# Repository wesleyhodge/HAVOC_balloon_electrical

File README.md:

# HAVOC\_balloon\_electrical

contains Kicad files for HAVOC

4.0 is the current 4.0 board

V3 is the eclipse model of HAVOC

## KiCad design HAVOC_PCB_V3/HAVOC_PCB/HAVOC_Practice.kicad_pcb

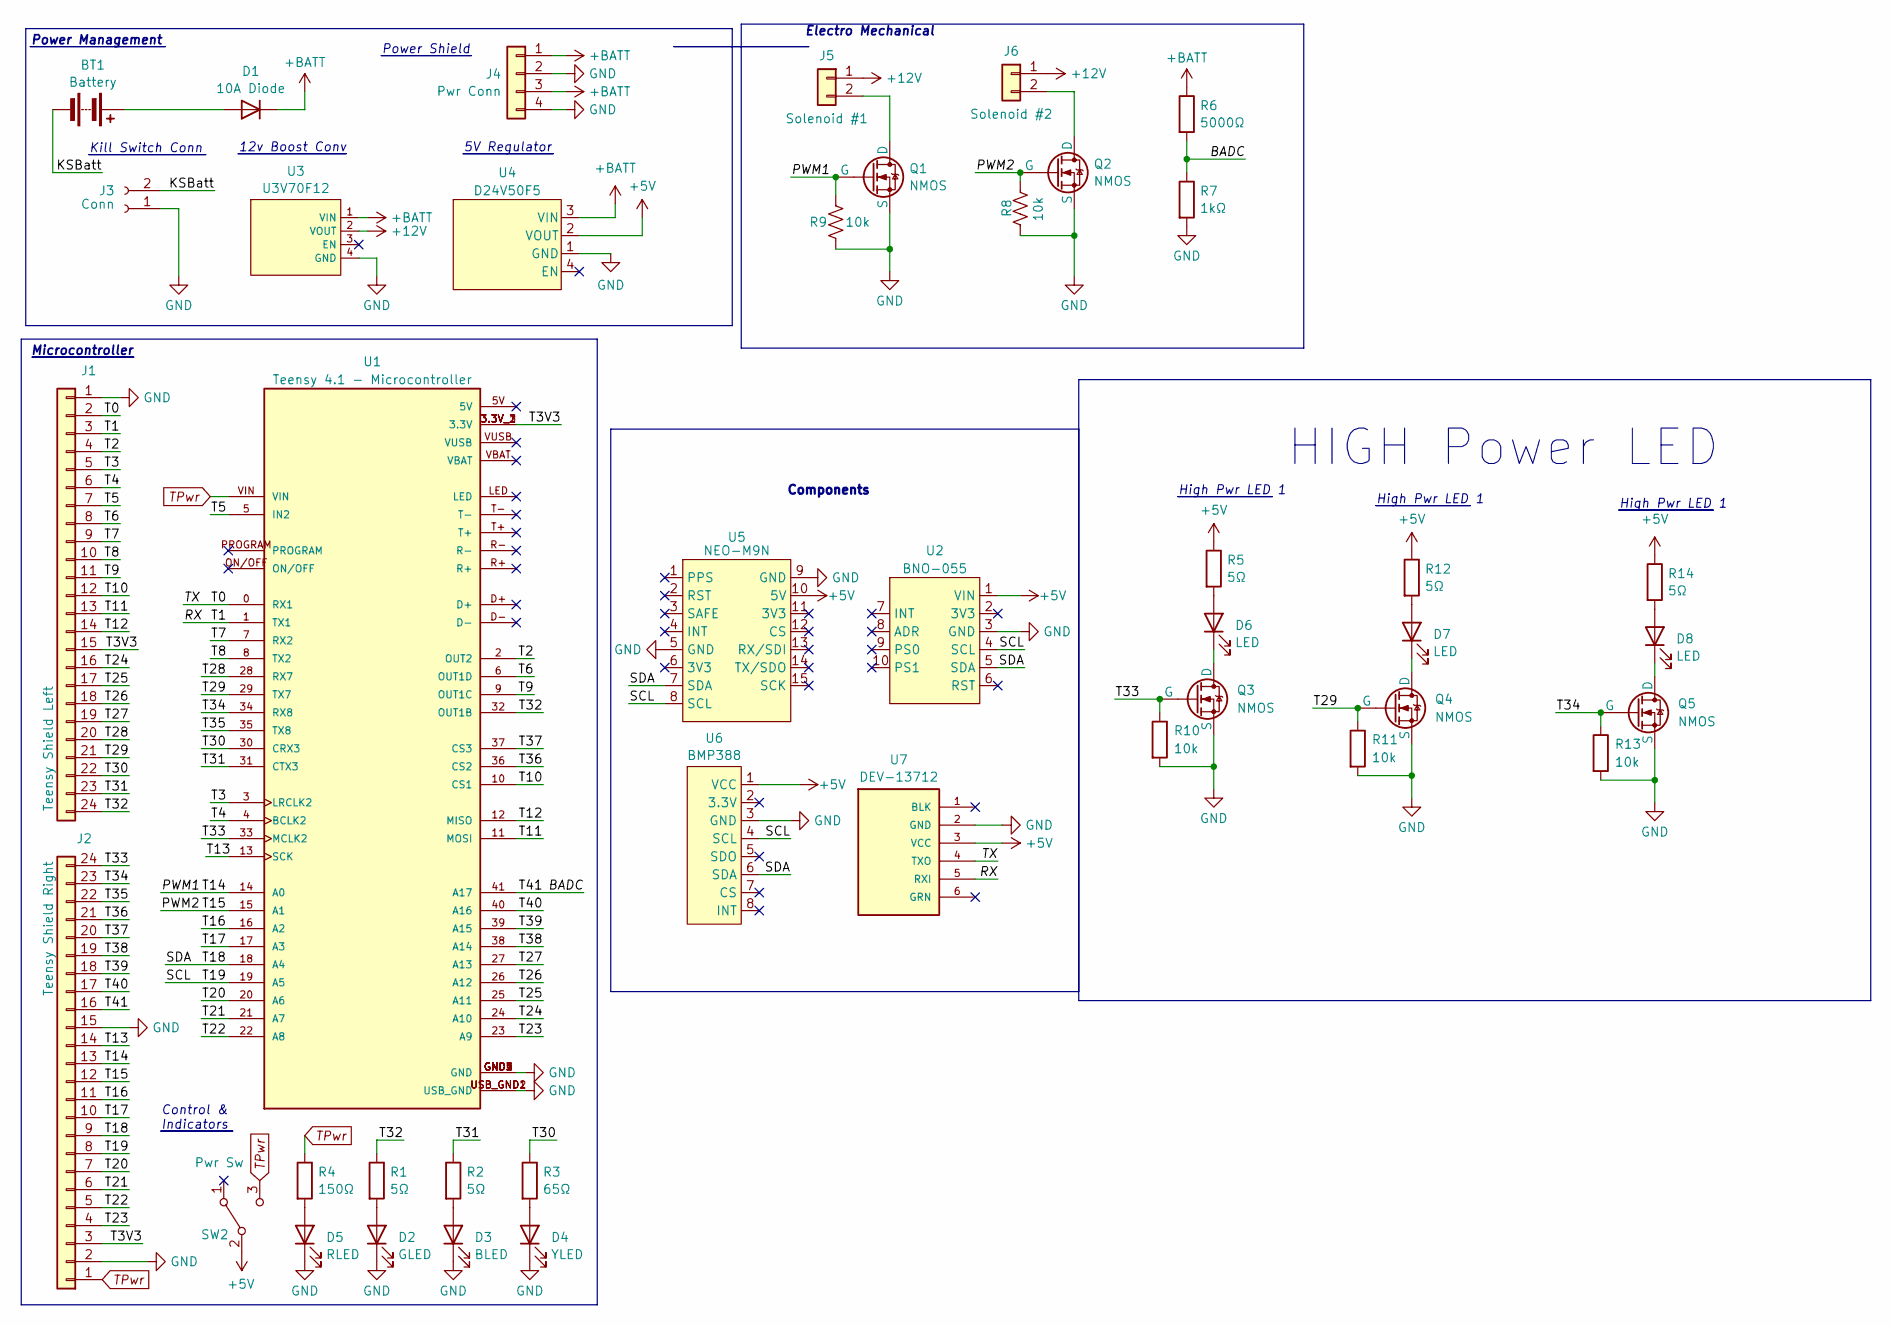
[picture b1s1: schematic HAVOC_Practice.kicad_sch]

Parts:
BT1: Battery; JST_XA_B02B-XASK-1_1x02_P2.50mm_Vertical
D1: 10A Diode; D_DO-34_SOD68_P2.54mm_Vertical_KathodeUp
D2: GLED; LED_150060VS55040
D3: BLED; LED_150060VS55040
D4: YLED; LED_150060VS55040
D5: RLED; LED_150060VS55040
D6, D7, D8: LED; JST_XA_B02B-XASK-1_1x02_P2.50mm_Vertical
J1: Teensy Shield Left; PinHeader_1x24_P2.54mm_Vertical
J2: Teensy Shield Right; PinHeader_1x24_P2.54mm_Vertical
J3: Conn; JST_XA_B02B-XASK-1_1x02_P2.50mm_Vertical
J4: Pwr Conn; PinHeader_1x04_P2.54mm_Vertical
J5: Solenoid #1; JST_XA_B02B-XASK-1_1x02_P2.50mm_Vertical
J6: Solenoid #2; JST_XA_B02B-XASK-1_1x02_P2.50mm_Vertical
Q1, Q2, Q3, Q4, Q5: NMOS; SOT23_DMG3406_DIO
R1, R2, R5, R12, R14: 5Ω; R_0603_1608Metric_Pad0.98x0.95mm_HandSolder
R3: 65Ω; R_0603_1608Metric_Pad0.98x0.95mm_HandSolder
R4: 150Ω; R_0603_1608Metric_Pad0.98x0.95mm_HandSolder
R6: 5000Ω; R_0603_1608Metric_Pad0.98x0.95mm_HandSolder
R7: 1kΩ; R_0603_1608Metric_Pad0.98x0.95mm_HandSolder
R8, R9, R10, R11, R13: 10k; R_0603_1608Metric_Pad0.98x0.95mm_HandSolder
SW2: Pwr Sw; SW_1101M2S3CQE2
U1: Teensy 4.1 - Microcontroller; MODULE_Teensy4-1; PARTREV 4.1
U2: BNO-055; BNO-055 Stemma Qt
U3: U3V70F12
U4: D24V50F5; Pololu 5v Reg
U5: NEO-M9N
U6: BMP388
U7: DEV-13712; OpenLog_DEV-13712; PARTREV v15; DigiKey_Part_Number 1568-1368-ND

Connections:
+5V: R5.1, R12.1, R14.1, SW2.2 (B), U2.1 (VIN), U4.2 (VOUT), U5.10 (5V), U6.1 (VCC), U7.3 (VCC)
+12V: J5.1, J6.1, U3.2 (VOUT)
+BATT: D1.1 (K), J4.1, J4.3, R6.1, U3.1 (VIN), U4.3 (VIN)
/BADC: J2.16, R6.2, R7.1, U1.41 (A17)
/KSBatt: BT1.2 (-), J3.2
/PWM1: J2.13, Q1.2 (G), R9.1, U1.14 (A0)
/PWM2: J2.12, Q2.2 (G), R8.1, U1.15 (A1)
/RX: J1.3, U1.1 (TX1), U7.5 (RXI)
/SCL: J2.8, U1.19 (A5), U2.4 (SCL), U5.8 (SCL), U6.4 (SCL)
/SDA: J2.9, U1.18 (A4), U2.5 (SDA), U5.7 (SDA), U6.6 (SDA)
/T0: J1.2, U1.0 (RX1), U7.4 (TXO)
/T2: J1.4, U1.2 (OUT2)
/T3: J1.5, U1.3 (LRCLK2)
/T3V3: J1.15, J2.3, U1.3.3V_1 (3.3V), U1.3.3V_2 (3.3V), U1.3.3V_3 (3.3V)
/T4: J1.6, U1.4 (BCLK2)
/T5: J1.7, U1.5 (IN2)
/T6: J1.8, U1.6 (OUT1D)
/T7: J1.9, U1.7 (RX2)
/T8: J1.10, U1.8 (TX2)
/T9: J1.11, U1.9 (OUT1C)
/T10: J1.12, U1.10 (CS1)
/T11: J1.13, U1.11 (MOSI)
/T12: J1.14, U1.12 (MISO)
/T13: J2.14, U1.13 (SCK)
/T16: J2.11, U1.16 (A2)
/T17: J2.10, U1.17 (A3)
/T20: J2.7, U1.20 (A6)
/T21: J2.6, U1.21 (A7)
/T22: J2.5, U1.22 (A8)
/T23: J2.4, U1.23 (A9)
/T24: J1.16, U1.24 (A10)
/T25: J1.17, U1.25 (A11)
/T26: J1.18, U1.26 (A12)
/T27: J1.19, U1.27 (A13)
/T28: J1.20, U1.28 (RX7)
/T29: J1.21, Q4.2 (G), R11.1, U1.29 (TX7)
/T30: J1.22, R3.1, U1.30 (CRX3)
/T31: J1.23, R2.1, U1.31 (CTX3)
/T32: J1.24, R1.1, U1.32 (OUT1B)
/T33: J2.24, Q3.2 (G), R10.1, U1.33 (MCLK2)
/T34: J2.23, Q5.2 (G), R13.1, U1.34 (RX8)
/T35: J2.22, U1.35 (TX8)
/T36: J2.21, U1.36 (CS2)
/T37: J2.20, U1.37 (CS3)
/T38: J2.19, U1.38 (A14)
/T39: J2.18, U1.39 (A15)
/T40: J2.17, U1.40 (A16)
GND: D2.1 (K), D3.1 (K), D4.1 (K), D5.1 (K), J1.1, J2.2, J2.15, J3.1, J4.2, J4.4, Q1.3 (S), Q2.3 (S), Q3.3 (S), Q4.3 (S), Q5.3 (S), R7.2, R8.2, R9.2, R10.2, R11.2, R13.2, U1.GND1 (GND), U1.GND2 (GND), U1.GND3 (GND), U1.GND4 (GND), U1.GND5 (GND), U1.USB_GND1 (USB_GND), U1.USB_GND2 (USB_GND), U2.3 (GND), U3.4 (GND), U4.1 (GND), U5.5 (GND), U5.9 (GND), U6.3 (GND), U7.2 (GND)
unnamed: BT1.1 (+), D1.2 (A)
unnamed: D2.2 (A), R1.2
unnamed: D3.2 (A), R2.2
unnamed: D4.2 (A), R3.2
unnamed: D5.2 (A), R4.2
unnamed: D6.2 (A), R5.2
unnamed: D6.1 (K), Q3.1 (D)
unnamed: D7.2 (A), R12.2
unnamed: D7.1 (K), Q4.1 (D)
unnamed: D8.2 (A), R14.2
unnamed: D8.1 (K), Q5.1 (D)
unnamed: J5.2, Q1.1 (D)
unnamed: J6.2, Q2.1 (D)
TPwr: J2.1, R4.1, SW2.3 (C), U1.VIN

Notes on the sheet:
12v Boost Conv
Control & Indicators
Components
High Pwr LED 1
5V Regulator
Electro Mechanical
Power Shield
Kill Switch Conn
Microcontroller
HIGH Power LED
Power Management

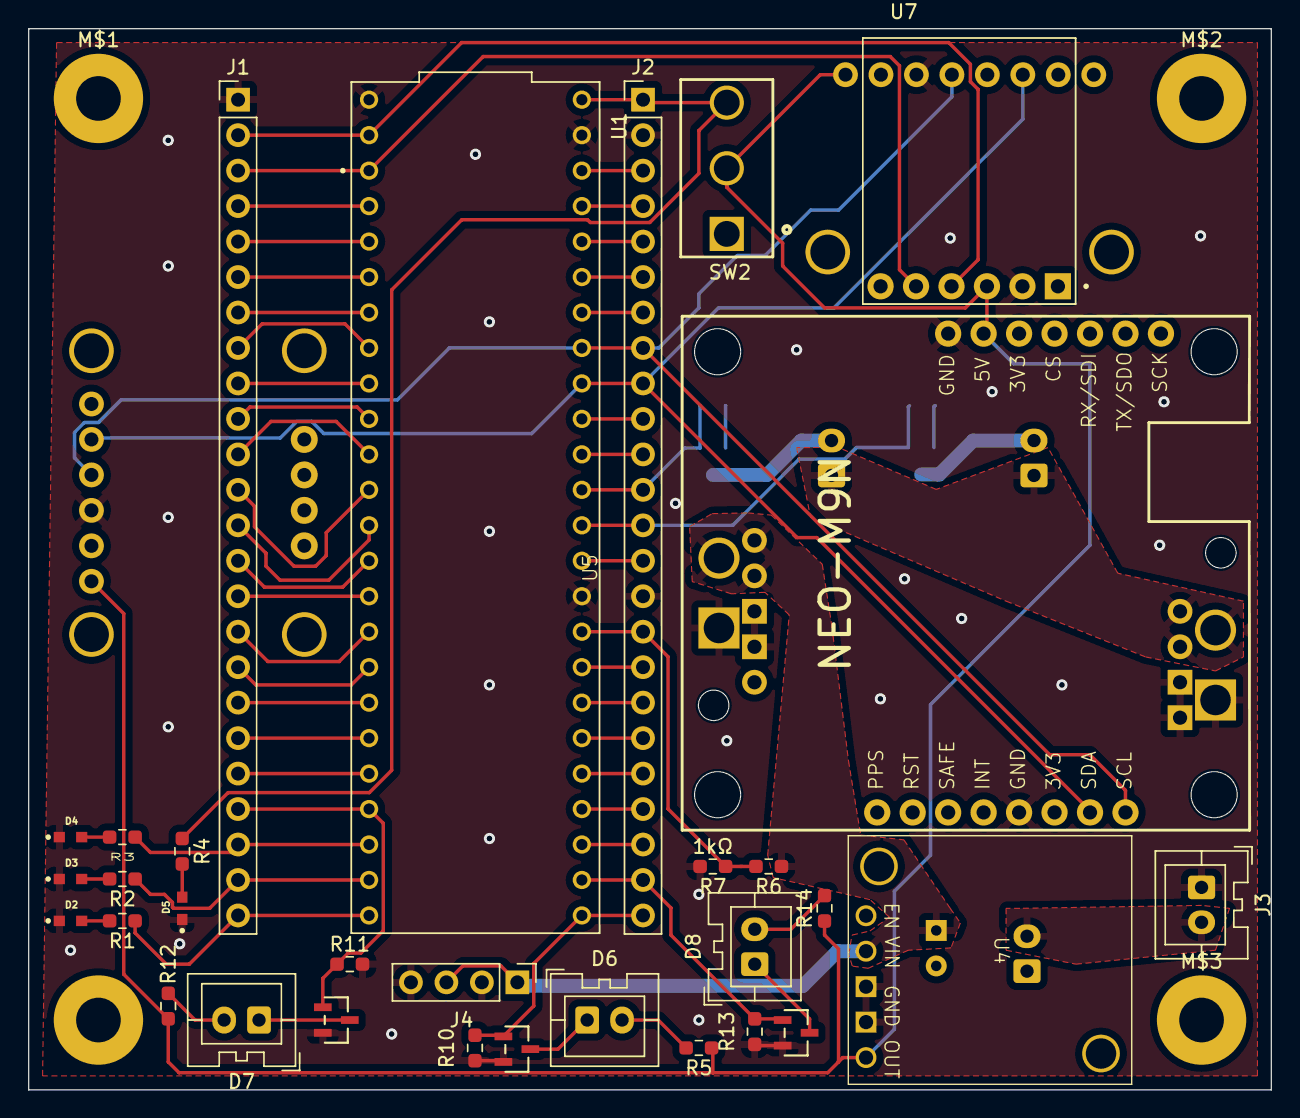
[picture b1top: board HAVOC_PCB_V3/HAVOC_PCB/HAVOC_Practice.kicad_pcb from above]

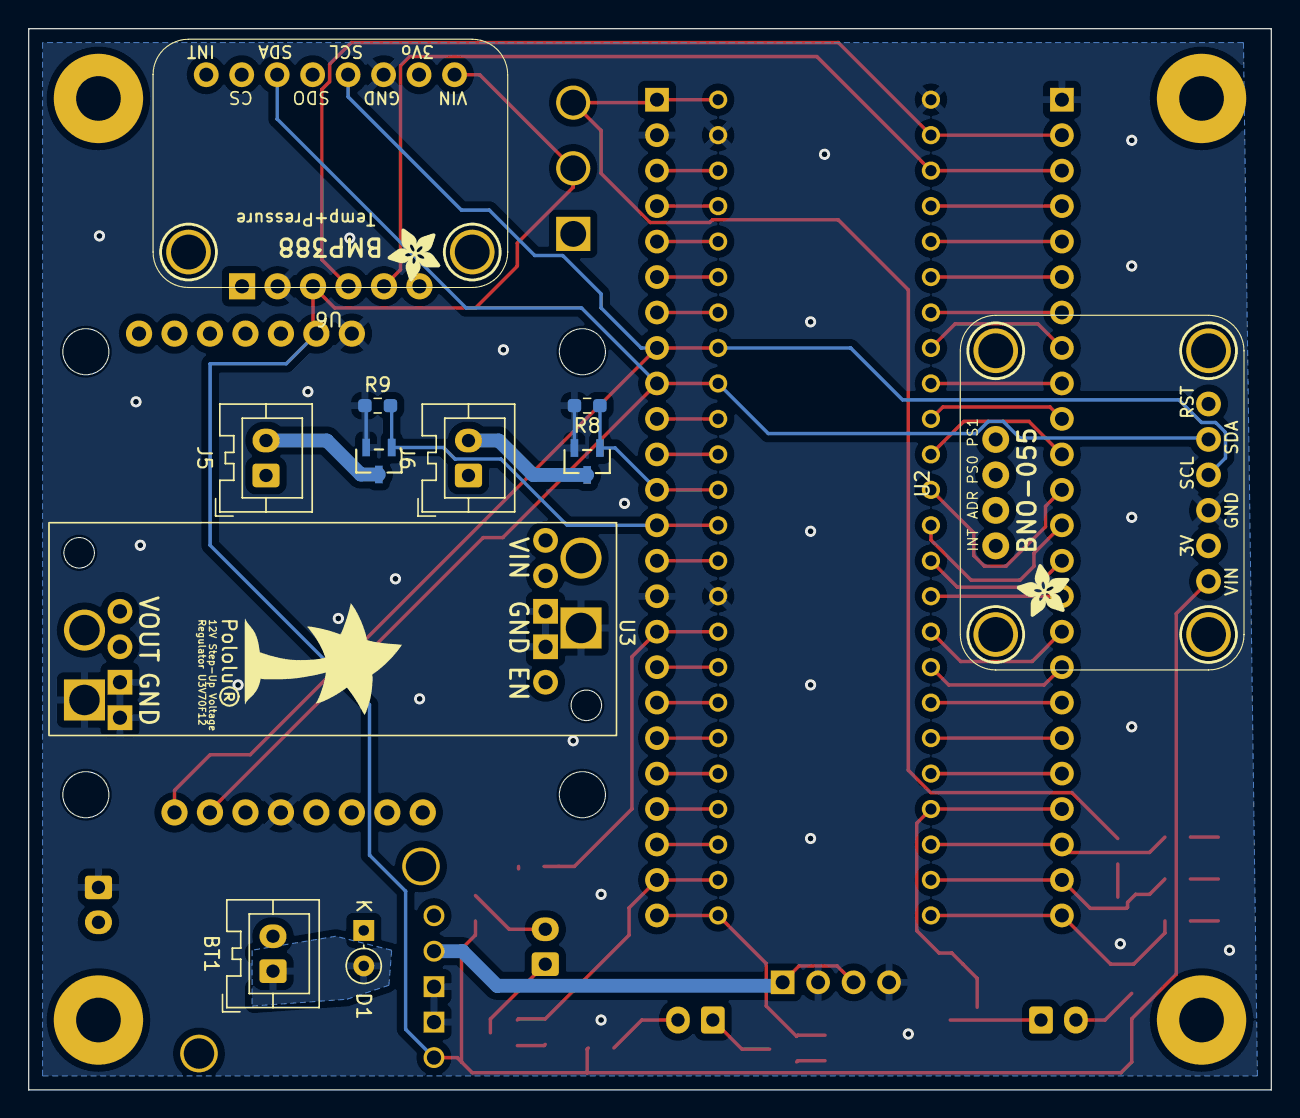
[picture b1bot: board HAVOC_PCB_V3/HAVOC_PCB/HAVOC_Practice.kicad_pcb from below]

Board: 2 copper layers, 89.0 x 76.0 mm, 46 parts (11 on the bottom side), 62 nets.

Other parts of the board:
M$1, M$2, M$3, M$4: MountingHole_3.2mm_M3_Pad

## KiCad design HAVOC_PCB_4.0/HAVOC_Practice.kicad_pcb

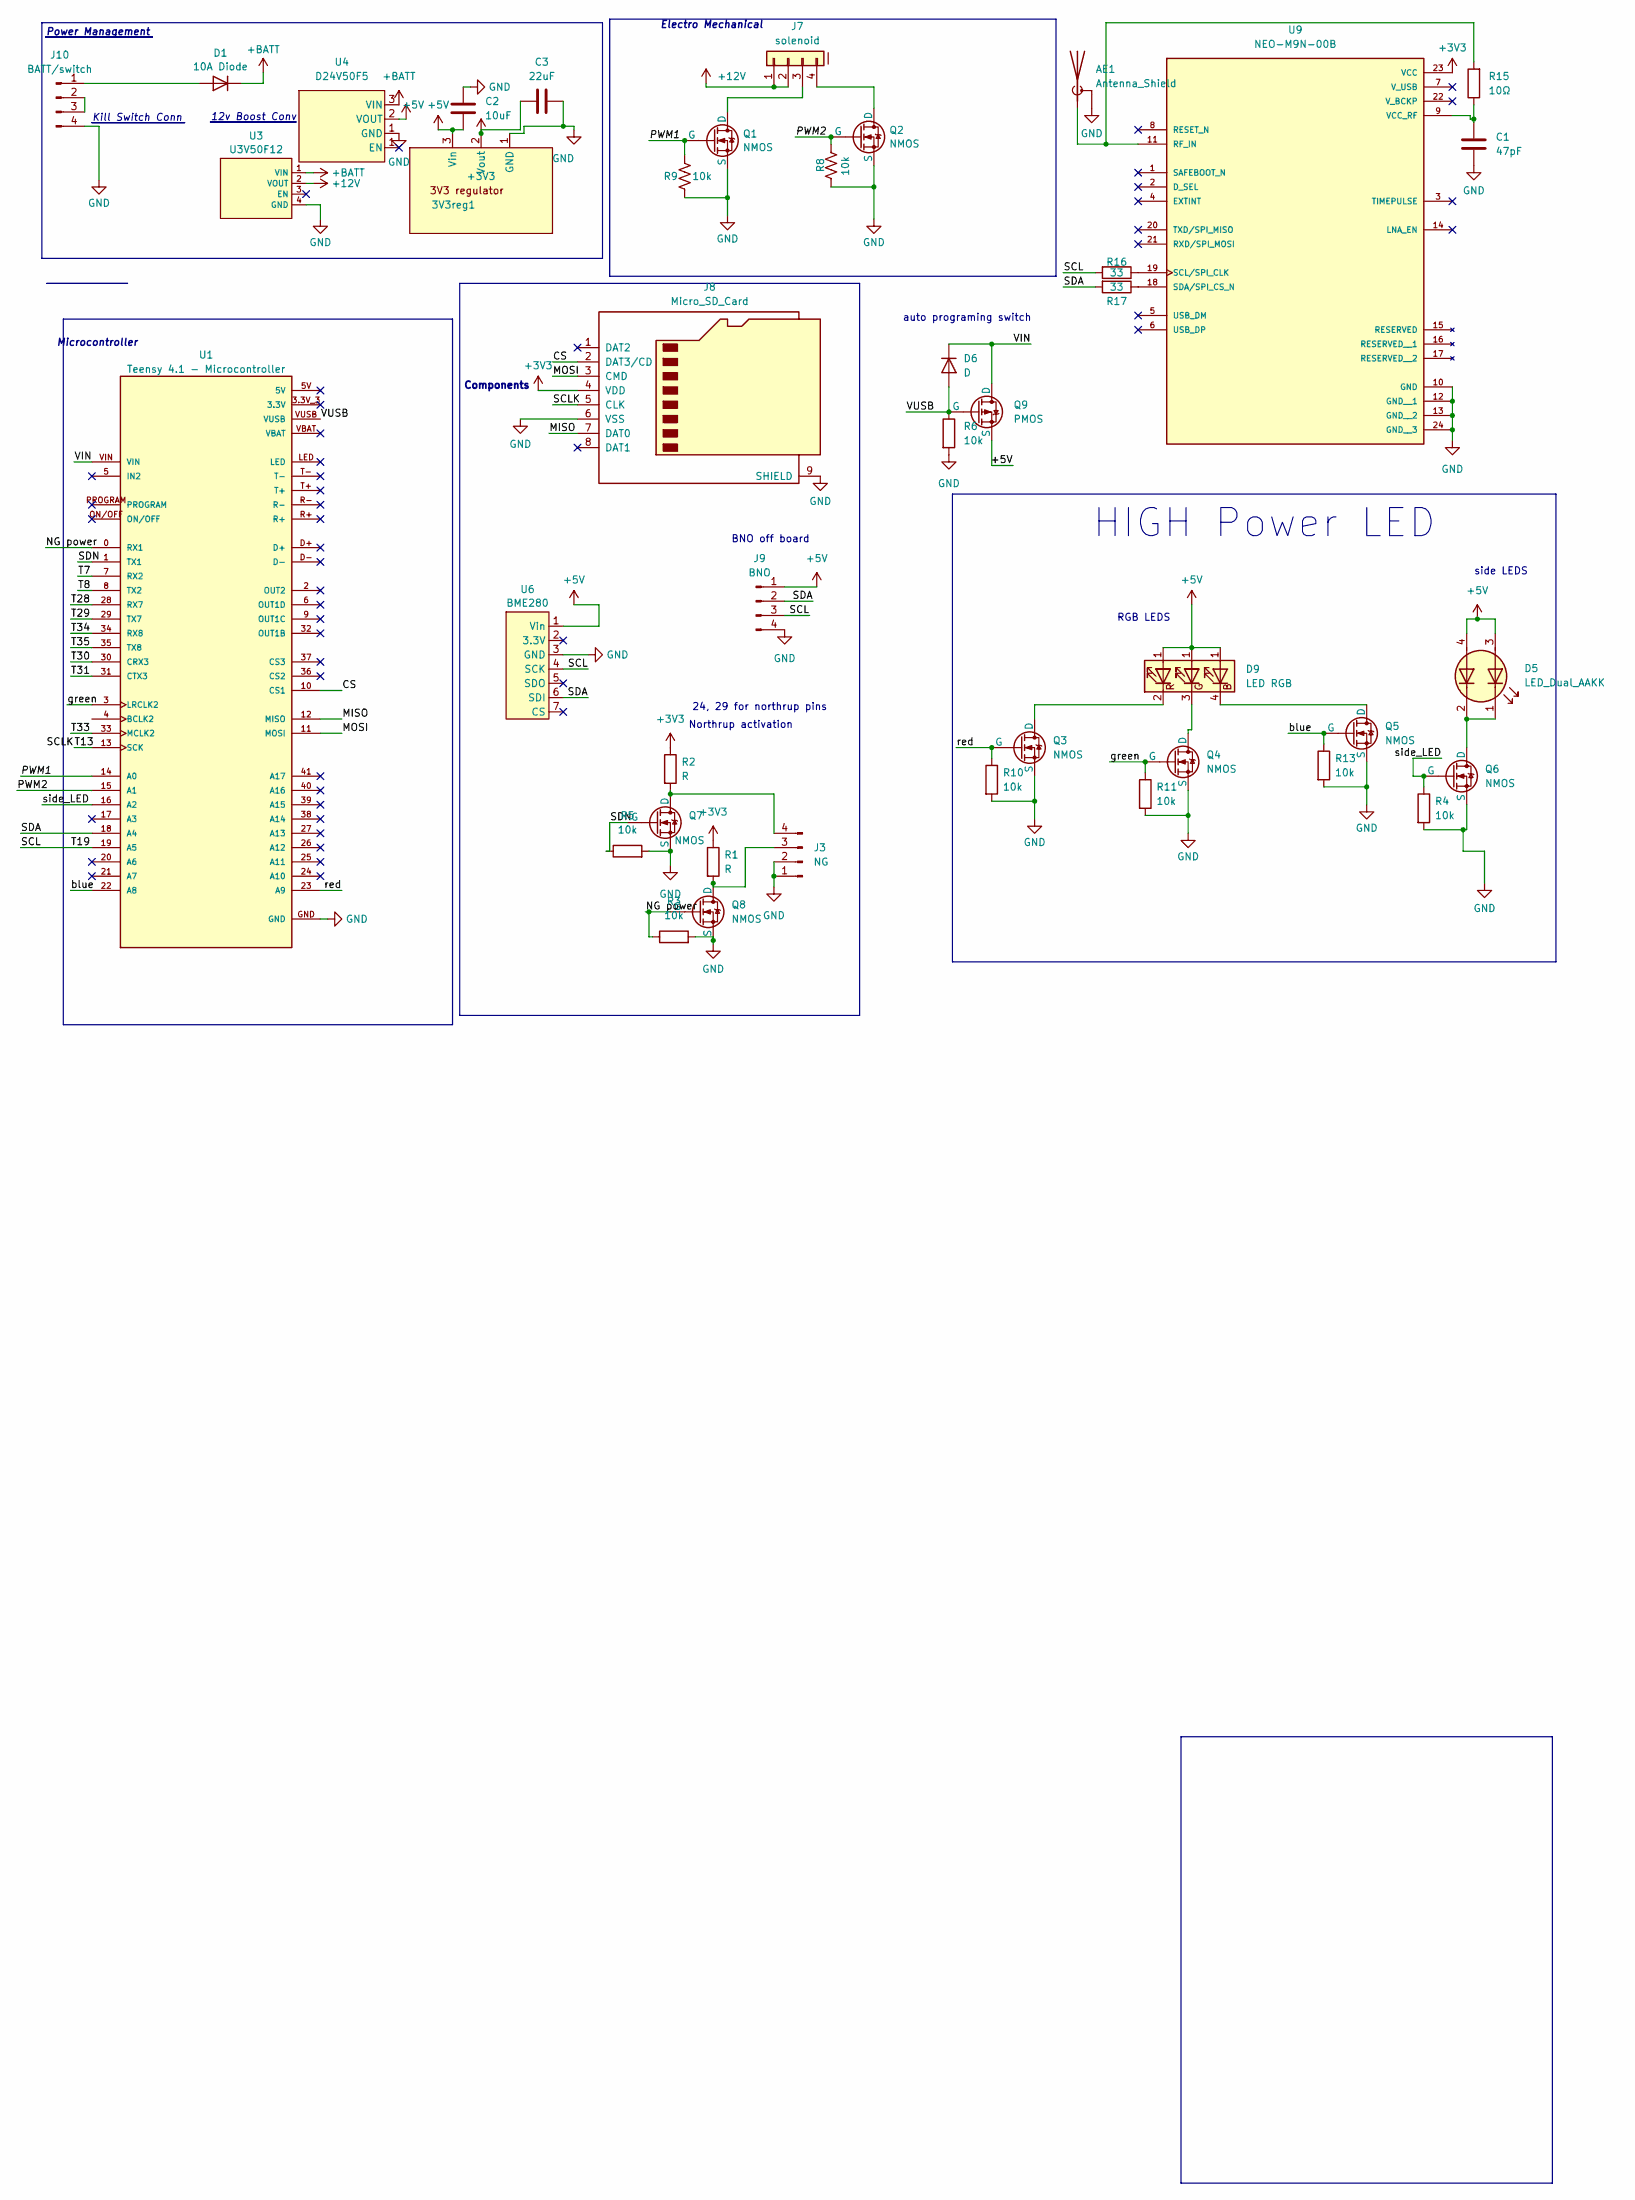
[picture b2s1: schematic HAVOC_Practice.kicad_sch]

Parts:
3V3reg1: SOT223-5_DIO-M
AE1: Antenna_Shield; antennaufl
C1: 47pF; C_0603_1608Metric_Pad1.08x0.95mm_HandSolder
C2: 10uF; C_0603_1608Metric_Pad1.08x0.95mm_HandSolder
C3: 22uF; C_0603_1608Metric_Pad1.08x0.95mm_HandSolder
D1: 10A Diode; HAVOC diode
D5: LED_Dual_AAKK; CONN4_S4B-XH_JST=SMD4pin
D6: D; HAVOC diode
D9: LED RGB; CONN4_S4B-XH_JST=SMD4pin
J3: NG; CONN4_S4B-XH_JST=SMD4pin
J7: solenoid; CONN4_S4B-XH_JST=SMD4pin
J8: Micro_SD_Card; SPI_SD
J9: BNO; CONN4_S4B-XH_JST=SMD4pin
J10: BATT/switch; CONN4_S4B-XH_JST=SMD4pin
Q1, Q2, Q3, Q4, Q5, Q6, Q7, Q8: NMOS; SOT23_DMG3406_DIO
Q9: PMOS; TO-220AB_LTO
R1, R2: R; R_0603_1608Metric_Pad0.98x0.95mm_HandSolder
R3, R4, R5, R6, R8, R9, R10, R11, R13: 10k; R_0603_1608Metric_Pad0.98x0.95mm_HandSolder
R15: 10Ω; R_0603_1608Metric_Pad0.98x0.95mm_HandSolder
R16, R17: 33; R_0603_1608Metric_Pad0.98x0.95mm_HandSolder
U1: Teensy 4.1 - Microcontroller; MODULE_Teensy4-1-H4.0; PARTREV 4.1
U3: U3V50F12; U3V50F12_12V_REG
U4: D24V50F5; Pololu 5v Reg
U6: BME280
U9: NEO-M9N-00B; XCVR_NEO-M9N-00B; PARTREV R05

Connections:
+3V3: 3V3reg1.2 (Vout), C3.2, J8.4 (VDD), R1.1, R2.1, U9.23 (VCC)
+5V: 3V3reg1.3 (Vin), C2.2, D5.3 (A1), D5.4 (A2), D9.1 (GA), J9.1, Q9.3 (S), U4.2 (VOUT), U6.1 (Vin)
+12V: J7.1, J7.2, U3.2 (VOUT)
+BATT: D1.1 (K), U3.1 (VIN), U4.3 (VIN)
/CS: J8.2 (DAT3/CD), U1.10 (CS1)
/MISO: J8.7 (DAT0), U1.12 (MISO)
/MOSI: J8.3 (CMD), U1.11 (MOSI)
/NG power: Q8.2 (G), R3.1, U1.0 (RX1)
/PWM1: Q1.2 (G), R9.1, U1.14 (A0)
/PWM2: Q2.2 (G), R8.1, U1.15 (A1)
/SCL: J9.3, R16.2, U1.19 (A5), U6.4 (SCK)
/SCLK: J8.5 (CLK), U1.13 (SCK)
/SDA: J9.2, R17.2, U1.18 (A4), U6.6 (SDI)
/SDN: Q7.2 (G), R5.1, U1.1 (TX1)
/T7: U1.7 (RX2)
/T8: U1.8 (TX2)
/T28: U1.28 (RX7)
/T29: U1.29 (TX7)
/T30: U1.30 (CRX3)
/T31: U1.31 (CTX3)
/T33: U1.33 (MCLK2)
/T34: U1.34 (RX8)
/T35: U1.35 (TX8)
/VIN: D6.1 (K), Q9.1 (D), U1.VIN
/VUSB: D6.2 (A), Q9.2 (G), R6.1, U1.VUSB
/blue: Q5.2 (G), R13.1, U1.22 (A8)
/green: Q4.2 (G), R11.1, U1.3 (LRCLK2)
/red: Q3.2 (G), R10.1, U1.23 (A9)
/side_LED: Q6.2 (G), R4.1, U1.16 (A2)
GND: 3V3reg1.1 (GND), AE1.2 (Shield), C1.2, C2.1, C3.1, J3.1, J3.2, J8.6 (VSS), J8.9 (SHIELD), J9.4, J10.4, Q1.3 (S), Q2.3 (S), Q3.3 (S), Q4.3 (S), Q5.3 (S), Q6.3 (S), Q7.3 (S), Q8.3 (S), R3.2, R4.2, R5.2, R6.2, R8.2, R9.2, R10.2, R11.2, R13.2, U1.GND, U3.4 (GND), U4.1 (GND), U6.3 (GND), U9.10 (GND), U9.12 (GND__1), U9.13 (GND__2), U9.24 (GND__3)
unnamed: AE1.1 (A), R15.2, U9.11 (RF_IN)
unnamed: D1.2 (A), J10.1
unnamed: D5.1 (K1), D5.2 (K2), Q6.1 (D)
unnamed: D9.4 (BK), Q5.1 (D)
unnamed: D9.3 (GK), Q4.1 (D)
unnamed: D9.2 (RK), Q3.1 (D)
unnamed: J3.3, Q8.1 (D), R1.2
unnamed: J3.4, Q7.1 (D), R2.2
unnamed: J7.3, Q1.1 (D)
unnamed: J10.2, J10.3
unnamed: J7.4, Q2.1 (D)
unnamed: R16.1, U9.19 (SCL/SPI_CLK)
unnamed: R17.1, U9.18 (SDA/SPI_CS_N)
unnamed: C1.1, R15.1, U9.9 (VCC_RF)

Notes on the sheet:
BNO off board
auto programing switch
12v Boost Conv
24, 29 for northrup pins
Components
Electro Mechanical
Kill Switch Conn
Microcontroller
Northrup activation
HIGH Power LED
Power Management
RGB LEDS
side LEDS

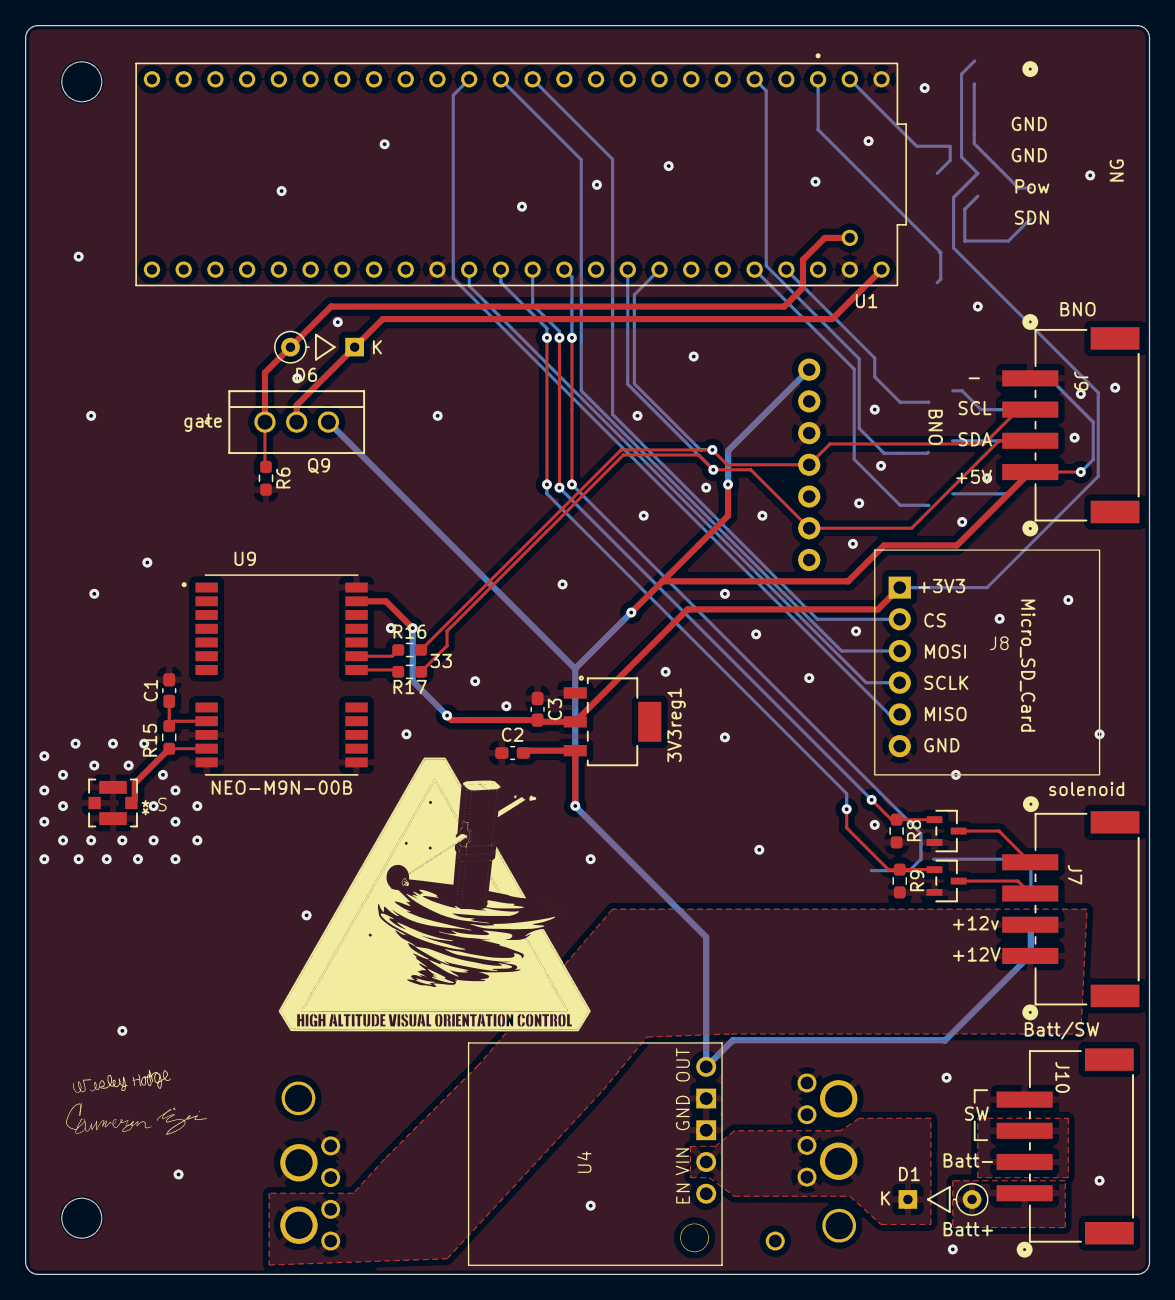
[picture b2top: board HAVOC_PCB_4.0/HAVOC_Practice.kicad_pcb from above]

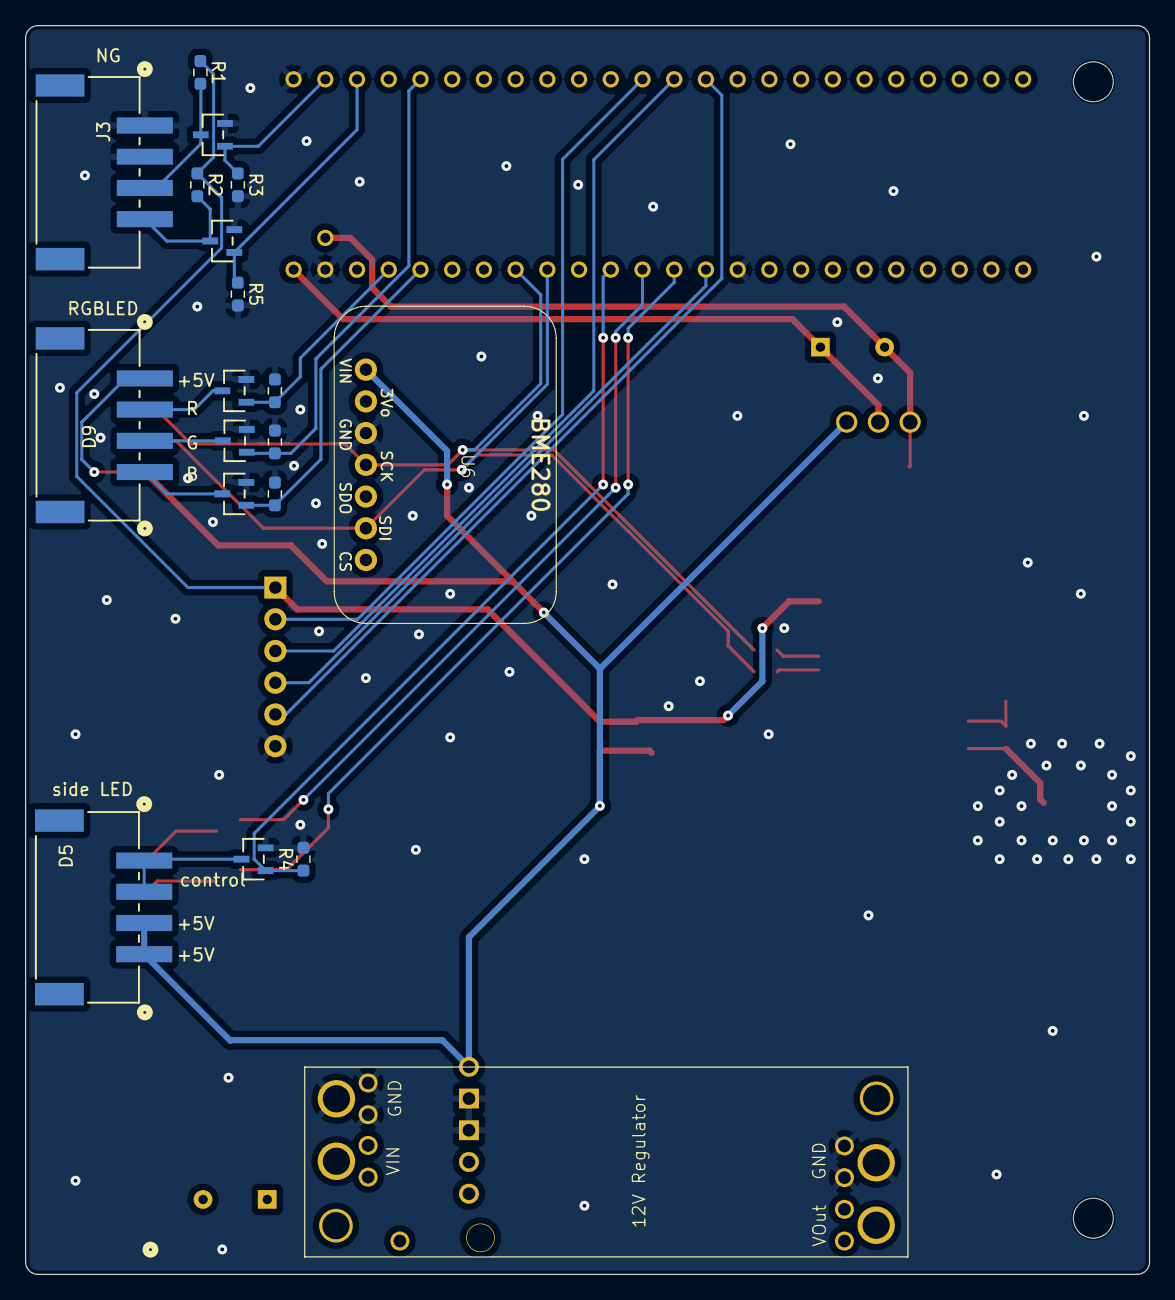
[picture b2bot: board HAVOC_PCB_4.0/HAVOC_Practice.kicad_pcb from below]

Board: 2 copper layers, 90.0 x 100.0 mm, 42 parts (19 on the bottom side), 35 nets.

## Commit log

2025-08-27 Populating Repository
2025-08-27 update to README
